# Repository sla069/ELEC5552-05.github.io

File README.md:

# Indoor Surveillance Drone
ELEC5552 Team 05 Indoor Surveillance Drone Project

An **autonomous indoor surveillance drone** built using the **Seeed Studio XIAO ESP32S3 Sense**, designed for **real-time monitoring, data collection, and wireless control**.  

---

## Overview

The Indoor Surveillance Drone is developed as part of a research and design project focused on indoor environmental surveillance without the use of GPS for the UWA Aviation Labs (UWAAL).  
It integrates a range of onboard sensors, live web dashboards, and local data storage to achieve semi-autonomous surveillance and sensing.

Key capabilities include:
- Real-time Wi-Fi access point (AP) control  
- Live sensor data viewing via web interface  
- Data logging in CSV format without a wired connection  
- Directional control of motors via web interface
- Live camera streaming and video recording

---

## Features

- Autonomous and manual operation modes  
- Web-based interface for live data and control  
- Wireless CSV data logging via Wi-Fi  
- Altitude, temperature, and motion sensing
- Wireless camera interface for live streaming and saving of footage to onboard microSD card

---

## Hardware Components

| Component | Description | Notes |
|------------|-------------|-------|
| **Seeed Studio XIAO ESP32S3 Sense** | Main MCU with camera and Wi-Fi | Handles all control, sensing, and communication |
| **Adafruit BMP280** | Pressure & temperature sensor | Used for altitude estimation |
| **Adafruit MPU6050** | 6-DOF IMU sensor | Provides acceleration and gyro data |
| **Li-Po Battery** | Power source | 3.7V rechargeable |
| **Drone Frame & Motors** | Propulsion system | Utilised for movement |
| **MicroSD** | Local memory | For video storage |

---

## Program Folders

This repository contains two main types of program folders, organized to make it clear which code is used for the **final demonstration** and which is for **prototyping or experiments**.

### `/src/` – Final Implemented Programs 

- Contains the **final versions** of the code used for demonstration.
- Each program is independent and can be uploaded separately to the XIAO ESP32S3.
- Subfolders:
  
/motor_control/wifi_controls.ino     → Controls drone motors and movement  
/camera_module/ESP32-CAM_MJPEG2SD.ino     → Handles camera functions and Wi-Fi streaming  
/sensor_module/combined_gyro_baro_pcb.ino       → Reads BMP280 + MPU6050 and serves web dashboard
- **Recommended for:** anyone testing or running the drone for the successfully achieved functionalities.  
- **Note:** The `camera_module` code is adapted from an open-source project ([ESP32-CAM_MJPEG2SD](https://github.com/s60sc/ESP32-CAM_MJPEG2SD)). See the `README.md` in that folder for proper attribution.

---

### `/prototype/` – Experimental and Prototype Code

- Contains **older, test, or experimental versions** of programs.
- Organized by purpose, phase, or subsystem. Example structure:

/individual_tests/→ initial motor, and sensor experiments   
/combined_versions/ → integrated tests before final firmware  
/superseded/ → older code no longer in use *(i.e for components no longer utilised in final design)*

---

## Setup and Installation

### Hardware Setup

| Connection | BMP280 | MPU6050 | Notes |
|-------------|---------|---------|-------|
| **SDA**     | GPIO 6  | GPIO 6  | Shared I2C line |
| **SCL**     | GPIO 7  | GPIO 7  | Shared I2C line |
| **VCC**     | 3.3V    | 3.3V    | Power supply |
| **GND**     | GND     | GND     | Common ground |

- Power the **Seeed Studio XIAO ESP32S3** or the motor circuit via a Li-Po battery. *(depending which functionality intended to use as the motor control circuit is powered on a different board)*
- Connect the onboard camera if using the camera module and ensure ESP+camera module are not connected on the PCB connectors.   

---

### Software Setup

1. **Install Prerequisites**
   - Download and install the [Arduino IDE](https://www.arduino.cc/en/software).  
   - Add ESP32 board support:
     - Go to *File → Preferences → Additional Board Manager URLs* and add:  
       ```
       https://dl.espressif.com/dl/package_esp32_index.json
       ```
     - Then open *Tools → Board → Boards Manager*, search **ESP32**, and install it.

2. **Install Required Libraries**
   In Arduino IDE, go to *Sketch → Include Library → Manage Libraries…* and install:
   - `Adafruit BMP280`
   - `Adafruit MPU6050`
   - `Adafruit Unified Sensor`
   - `WiFi`
   - `WebServer`
   - `FS` / `SPIFFS`

3. **Clone the Repository**
   ```bash
   git clone https://github.com/<sla069>/ELEC5502-05.git
   cd ELEC5502-05

*(If you’re using Arduino IDE only, you can skip the terminal step — just click **Code → Download ZIP**, then extract the files manually.)*

### Flashing programs

1. **Select which functionality to upload.**
   - Open the desired .ino file in Arduino IDE depending on which subsystem you want to test or run.
   - Each file should be uploaded separately to the ESP dev board as a standalone program.

2. **Board Configuration**
   - Go to Tools → Board and select Seeed XIAO ESP32S3
   - Choose the correct COM port under Tools → Port.
  
3. **Compile and Upload**

4. **Access Web Interfaces**
   - For the motor module:
     - Connect to the wifi network: ESP_DRONE
     - Open your browser and navigate to: http://192.168.4.1/

   - For the sensors:
     - Connect to the wifi network: Drone_sensors
     - Open your browser and navigate to: http://192.168.4.1/
    
   - For the camera module:
     - Connect to the wifi network: Drone Live Footage
     - Open your browser and navigate to: http://192.168.4.1/

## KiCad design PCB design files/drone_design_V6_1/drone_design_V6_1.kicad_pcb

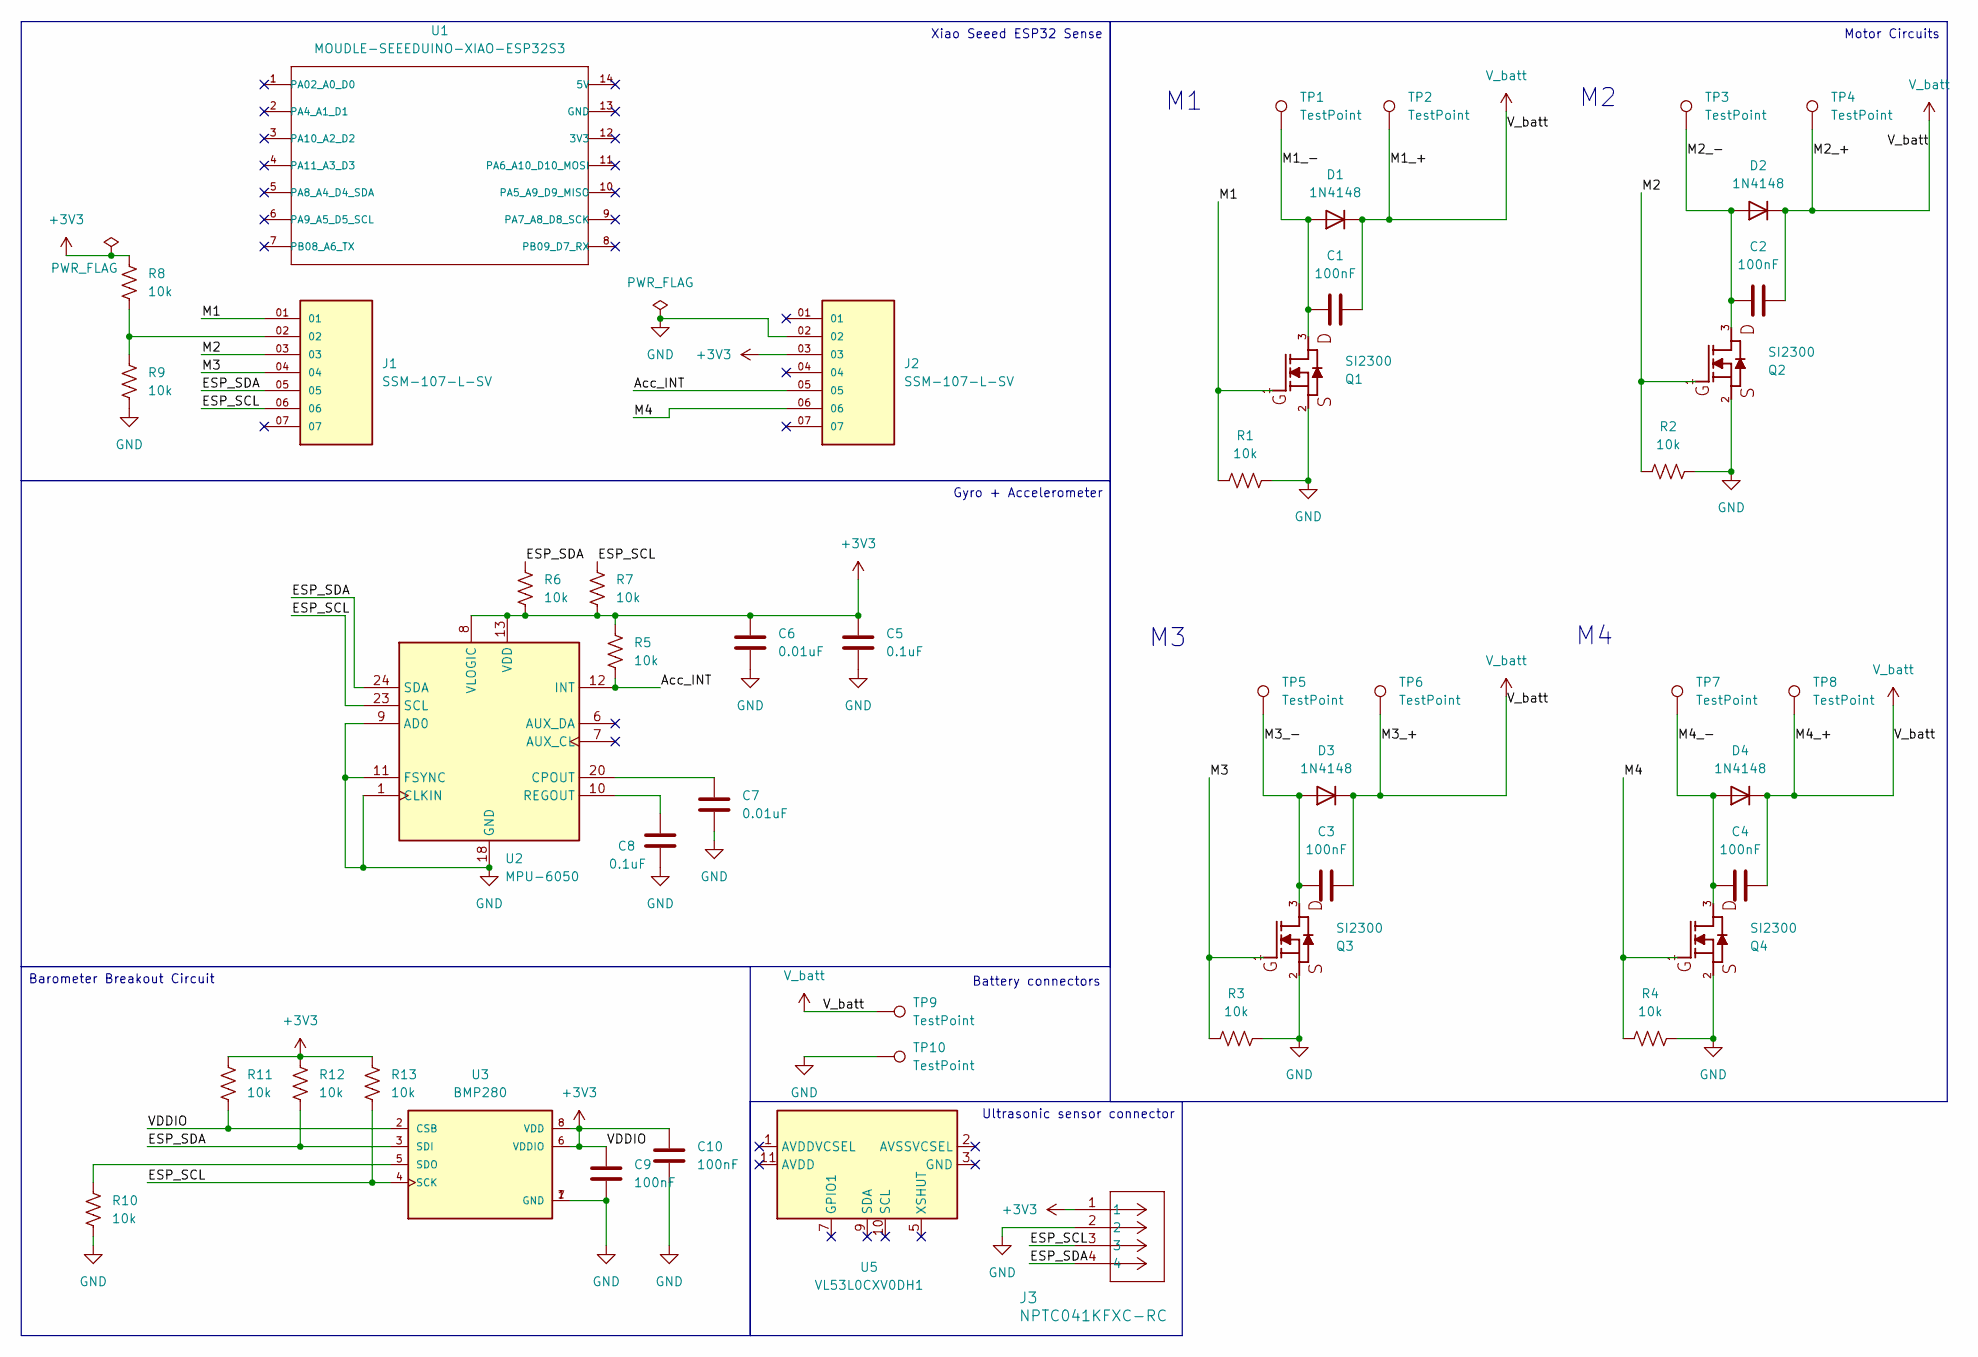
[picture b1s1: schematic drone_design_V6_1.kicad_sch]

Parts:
C1, C2, C3, C4, C9, C10: 100nF; C_0805_2012Metric
C5, C8: 0.1uF; C_0805_2012Metric
C6, C7: 0.01uF; C_0805_2012Metric
D1, D2, D3, D4: 1N4148; D_SOD-123
J1, J2: SSM-107-L-SV; SAMTEC_SSM-107-L-SV
J3: NPTC041KFXC-RC; CONN4X1_NPTC041KFXC-RC_SUL
Q1, Q2, Q3, Q4: SI2300; SOT-23
R1, R2, R3, R4, R5, R6, R7, R8, R9, R10, R11, R12, R13: 10k; C_0805_2012Metric
TP1, TP2, TP3, TP4, TP5, TP6, TP7, TP8: TestPoint; TestPoint_Pad_D1.5mm
TP9, TP10: TestPoint; TestPoint_Pad_D1.0mm
U1: MOUDLE-SEEEDUINO-XIAO-ESP32S3; MOUDLE14P-SMD-2.54-21X17.8MM
U2: MPU-6050; InvenSense_QFN-24_4x4mm_P0.5mm
U3: BMP280; XDCR_BMP280; PART_REV 1.19
U5: VL53L0CXV0DH1; ST_VL53L1x

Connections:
+3V3: C5.1, C6.1, C9.1, C10.1, J2.03, J3.1, R5.1, R6.2, R7.2, R8.2, R11.1, R11.2, R12.1, R13.1, U2.8 (VLOGIC), U2.13 (VDD), U3.2 (CSB), U3.6 (VDDIO), U3.8 (VDD)
/Acc_INT: J2.05, R5.2, U2.12 (INT)
/ESP_SCL: J1.06, J3.3, R7.1, R13.2, U2.23 (SCL), U3.4 (SCK)
/ESP_SDA: J1.05, J3.4, R6.1, R12.2, U2.24 (SDA), U3.3 (SDI)
/M1: J1.01, Q1.1, R1.1
/M1_-: C1.1, D1.2 (A), Q1.3, TP1.1
/M2: J1.03, Q2.1, R2.1
/M2_-: C2.1, D2.2 (A), Q2.3, TP3.1
/M3: J1.04, Q3.1, R3.1
/M3_-: C3.1, D3.2 (A), Q3.3, TP5.1
/M4: J2.06, Q4.1, R4.1
/M4_-: C4.1, D4.2 (A), Q4.3, TP7.1
GND: C5.2, C6.2, C7.2, C8.2, C9.2, C10.2, J2.02, J3.2, Q1.2, Q2.2, Q3.2, Q4.2, R1.2, R2.2, R3.2, R4.2, R9.1, R10.2, TP10.1, U2.1 (CLKIN), U2.9 (AD0), U2.11 (FSYNC), U2.18 (GND), U3.1 (GND), U3.7 (GND)
unnamed: J1.02, R8.1, R9.2
unnamed: C7.1, U2.20 (CPOUT)
unnamed: C8.1, U2.10 (REGOUT)
unnamed: R10.1, U3.5 (SDO)
unnamed: U5.3 (GND), U5.4 (GND), U5.6 (GND), U5.12 (GND)
V_batt: C1.2, C2.2, C3.2, C4.2, D1.1 (K), D2.1 (K), D3.1 (K), D4.1 (K), TP2.1, TP4.1, TP6.1, TP8.1, TP9.1

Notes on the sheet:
Battery connectors
Ultrasonic sensor connector
Gyro + Accelerometer
Xiao Seeed ESP32 Sense
Barometer Breakout Circuit
Motor Circuits

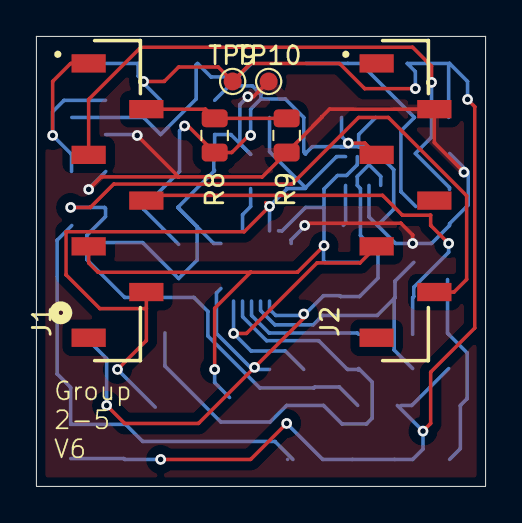
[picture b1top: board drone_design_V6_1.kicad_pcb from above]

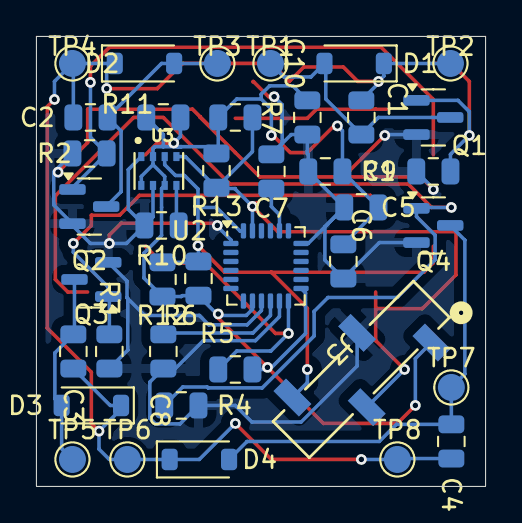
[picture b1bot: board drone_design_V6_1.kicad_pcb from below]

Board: 2 copper layers, 25.0 x 25.0 mm, 46 parts (40 on the bottom side), 18 nets.

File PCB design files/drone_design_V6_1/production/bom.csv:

Designator,Footprint,Quantity,Value,LCSC Part #
"C1, C10, C2, C3, C4, C9",0805,6,100nF,
"C5, C8",0805,2,0.1uF,
"C6, C7",0805,2,0.01uF,
"D1, D2, D3, D4",D_SOD-123,4,1N4148,
"J1, J2",SAMTEC_SSM-107-L-SV,2,SSM-107-L-SV,
J3,CONN4X1_NPTC041KFXC-RC_SUL,1,NPTC041KFXC-RC,
"Q1, Q2, Q3, Q4",SOT-23,4,SI2300,
"R1, R10, R11, R12, R13, R2, R3, R4, R5, R6, R7, R8, R9",0805,13,10k,
"TP1, TP2, TP3, TP4, TP5, TP6, TP7, TP8",TestPoint_Pad_D1.5mm,8,TestPoint,
"TP10, TP9",TestPoint_Pad_D1.0mm,2,TestPoint,
U2,InvenSense_QFN-24_4x4mm_P0.5mm,1,MPU-6050,
U3,XDCR_BMP280,1,BMP280,

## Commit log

2025-10-24 Add initial PCB schematic file
2025-10-24 Update and rename PCB to note
2025-10-24 Update note
2025-10-27 Create NOTE
2025-10-27 Create previous versions
2025-10-27 Create blank
2025-10-27 Add blank file in sensor_module directory
2025-10-27 Add new camera module file 'b'
2025-10-27 Create b
2025-10-27 README updated
2025-10-27 wifi_controls.ino uploaded
2025-10-27 combined_gyro_baro_pcb.ino uploaded
2025-10-27 update README with program folder structure
    Added detailed sections for program organization, including final implemented programs and experimental code.
2025-10-27 Create a
2025-10-27 upload files
2025-10-29 Create p
2025-10-29 Create LICENSE
